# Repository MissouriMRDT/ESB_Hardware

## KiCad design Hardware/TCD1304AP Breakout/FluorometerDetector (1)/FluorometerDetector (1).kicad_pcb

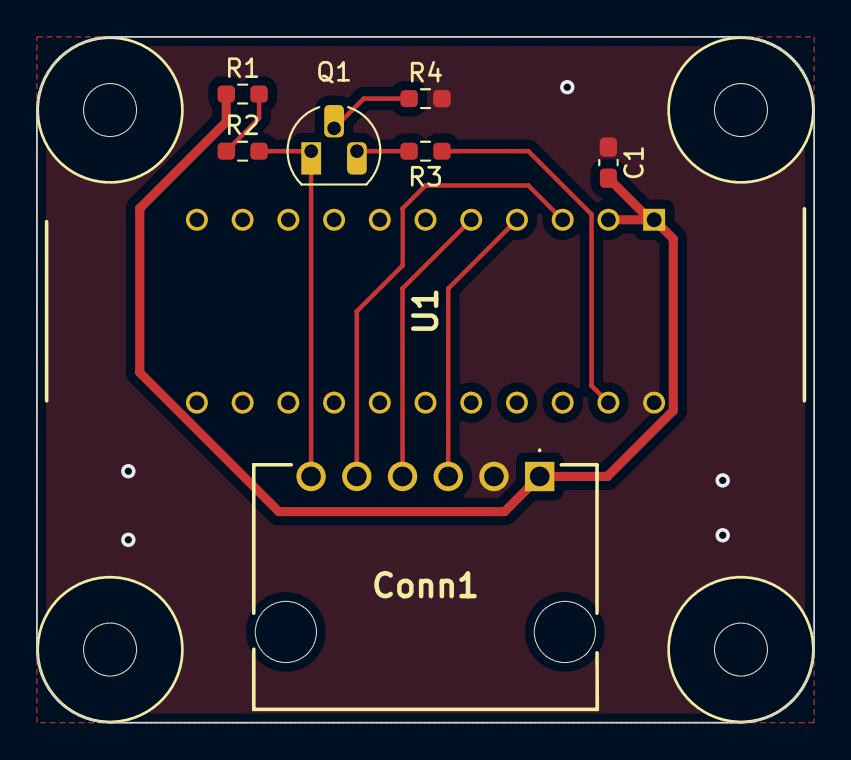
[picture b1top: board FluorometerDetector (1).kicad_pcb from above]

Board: 2 copper layers, 43.2 x 38.1 mm, 12 parts (0 on the bottom side), 10 nets.

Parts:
C1: 10uF; C_0603_1608Metric_Pad1.08x0.95mm_HandSolder
Conn1: Molex_SL_06; 705550040
Q1: Q_PNP_BCE; TO-92_HandSolder
R1: 1.2k; R_0603_1608Metric_Pad0.98x0.95mm_HandSolder
R2: 1k; R_0603_1608Metric_Pad0.98x0.95mm_HandSolder
R3, R4: 150; R_0603_1608Metric_Pad0.98x0.95mm_HandSolder
U1: TCD1304; DIP1016W62P254L4160H372Q22N
V1, V2, V3, V4: Via; 4_40_Hole

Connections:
+3V3: C1.2, Conn1.1, R1.1, U1.1 (VDD), U1.2 (VAD)
GND: C1.1, Conn1.2, R4.2, U1.22 (SS)
unnamed: Conn1.3, U1.4 (M)
unnamed: Conn1.4, U1.5 (SH)
unnamed: Conn1.5, U1.3 (ICG)
unnamed: Conn1.6, Q1.1 (E), R2.2
unnamed: Q1.2 (C), R4.1
unnamed: Q1.3 (B), R3.2
unnamed: R1.2, R2.1
unnamed: R3.1, U1.21 (OS)

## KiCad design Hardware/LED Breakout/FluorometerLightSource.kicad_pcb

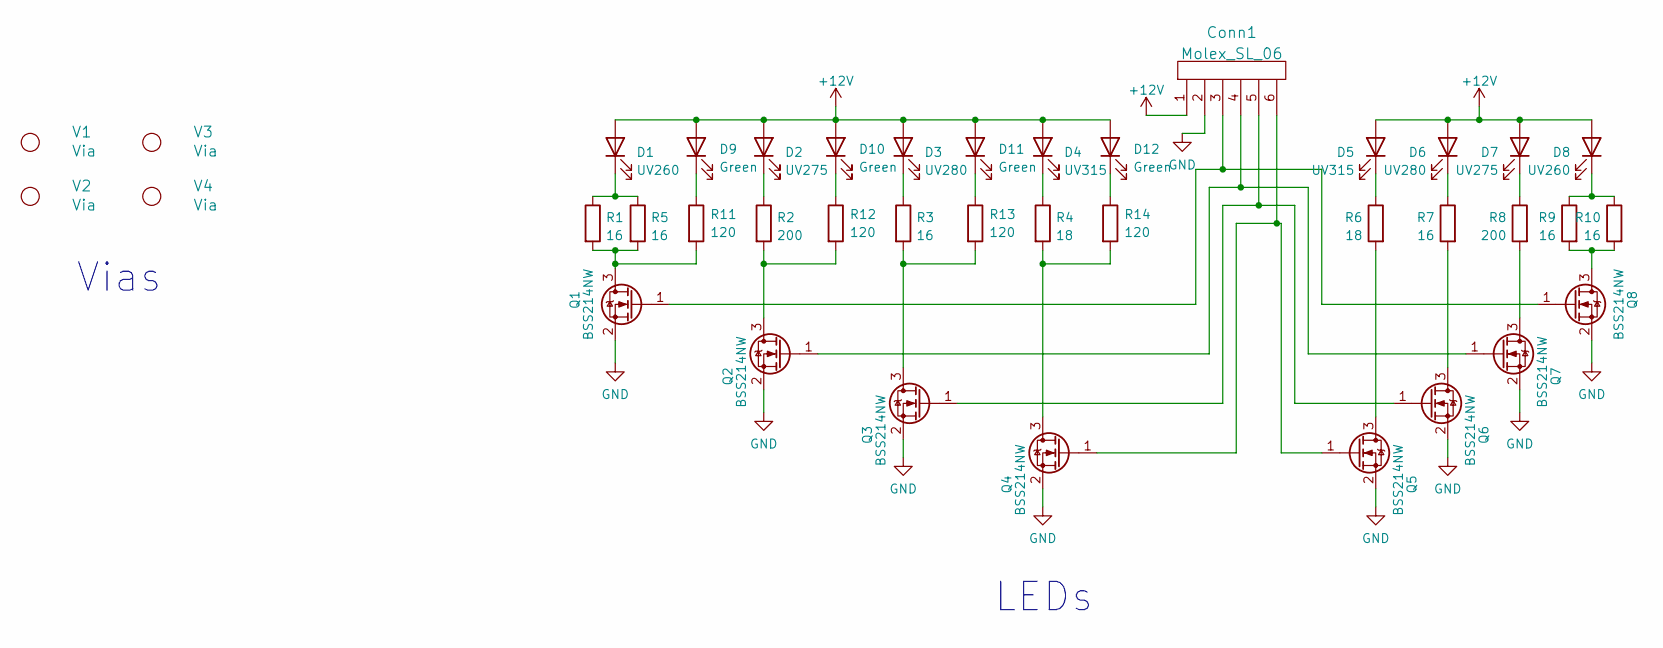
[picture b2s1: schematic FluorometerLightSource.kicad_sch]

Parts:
Conn1: Molex_SL_06; 705550040
D1, D8: UV260; KL26550USMWD
D2, D7: UV275; SUCULBN1VCAGAY674F4G30R18
D3, D6: UV280; XBT3535UVA130CD27501
D4, D5: UV315; WS3535C48LF-310
D9, D10, D11, D12: Green; LED_0603_1608Metric_Pad1.05x0.95mm_HandSolder
Q1, Q2, Q3, Q4, Q5, Q6, Q7, Q8: BSS214NW; SOT-323_SC-70
R1, R3, R5, R7, R9, R10: 16; R_2512_6332Metric_Pad1.40x3.35mm_HandSolder
R2, R8: 200; R_0603_1608Metric_Pad0.98x0.95mm_HandSolder
R4, R6: 18; R_2512_6332Metric_Pad1.40x3.35mm_HandSolder
R11, R12, R13, R14: 120; R_0603_1608Metric_Pad0.98x0.95mm_HandSolder
V1, V2, V3, V4: Via; 4_40_Hole

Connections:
+12V: Conn1.1, D1.2 (A), D2.2 (A), D3.2 (A), D4.2 (A), D5.2 (A), D6.2 (A), D7.2 (A), D8.2 (A), D9.2 (A), D10.2 (A), D11.2 (A), D12.2 (A)
GND: Conn1.2, Q1.2 (S), Q2.2 (S), Q3.2 (S), Q4.2 (S), Q5.2 (S), Q6.2 (S), Q7.2 (S), Q8.2 (S)
unnamed: Conn1.3, Q1.1 (G), Q8.1 (G)
unnamed: Conn1.4, Q2.1 (G), Q7.1 (G)
unnamed: Conn1.5, Q3.1 (G), Q6.1 (G)
unnamed: Conn1.6, Q4.1 (G), Q5.1 (G)
unnamed: D1.1 (K), R1.1, R5.1
unnamed: D2.1 (K), R2.1
unnamed: D3.1 (K), R3.1
unnamed: D4.1 (K), R4.1
unnamed: D5.1 (K), R6.1
unnamed: D6.1 (K), R7.1
unnamed: D7.1 (K), R8.1
unnamed: D8.1 (K), R9.1, R10.1
unnamed: D9.1 (K), R11.1
unnamed: D10.1 (K), R12.1
unnamed: D11.1 (K), R13.1
unnamed: D12.1 (K), R14.1
unnamed: Q1.3 (D), R1.2, R5.2, R11.2
unnamed: Q2.3 (D), R2.2, R12.2
unnamed: Q3.3 (D), R3.2, R13.2
unnamed: Q4.3 (D), R4.2, R14.2
unnamed: Q5.3 (D), R6.2
unnamed: Q6.3 (D), R7.2
unnamed: Q7.3 (D), R8.2
unnamed: Q8.3 (D), R9.2, R10.2

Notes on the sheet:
LEDs
Vias

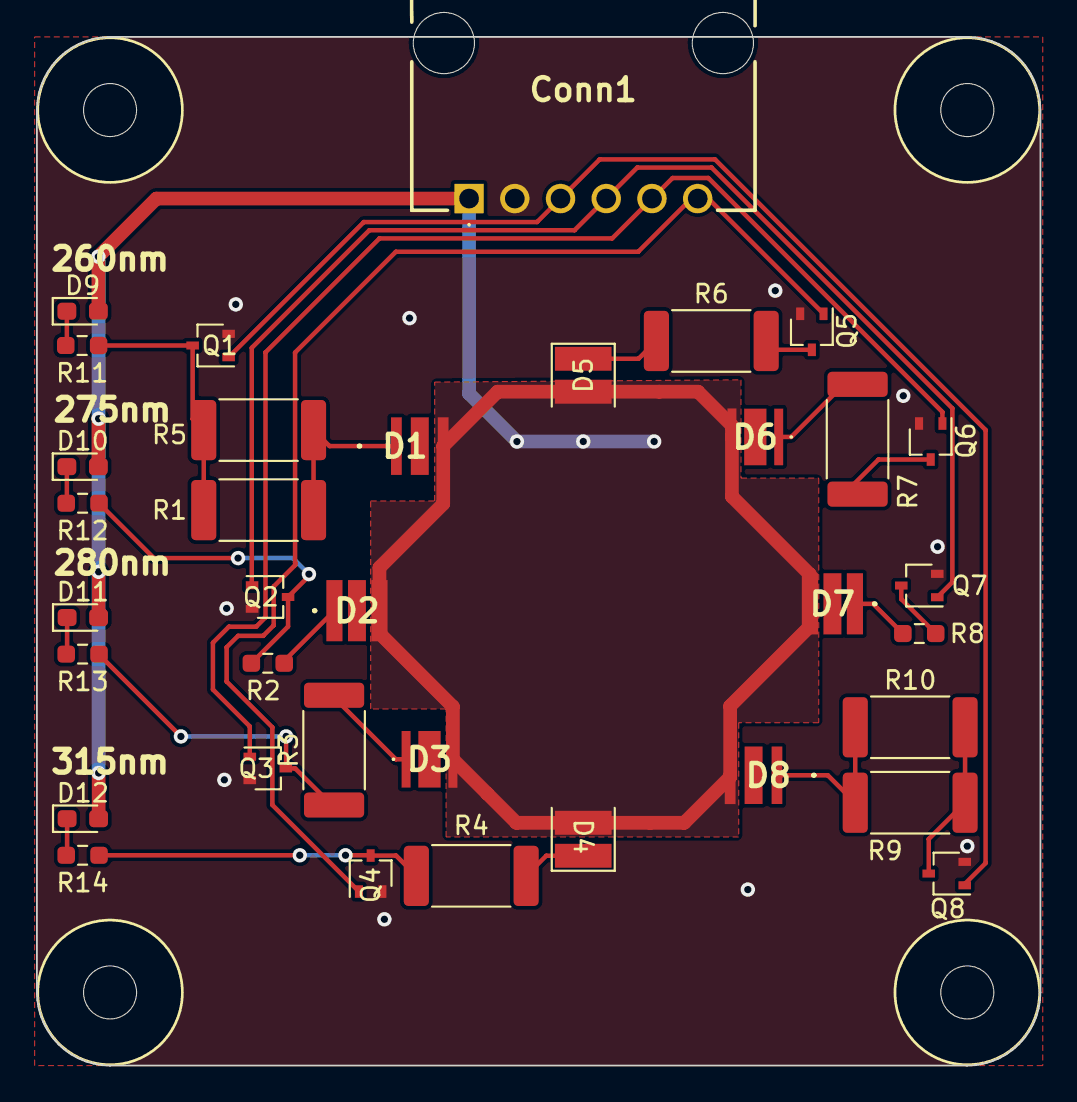
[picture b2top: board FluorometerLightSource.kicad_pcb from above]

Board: 2 copper layers, 55.8 x 57.1 mm, 39 parts (0 on the bottom side), 26 nets.

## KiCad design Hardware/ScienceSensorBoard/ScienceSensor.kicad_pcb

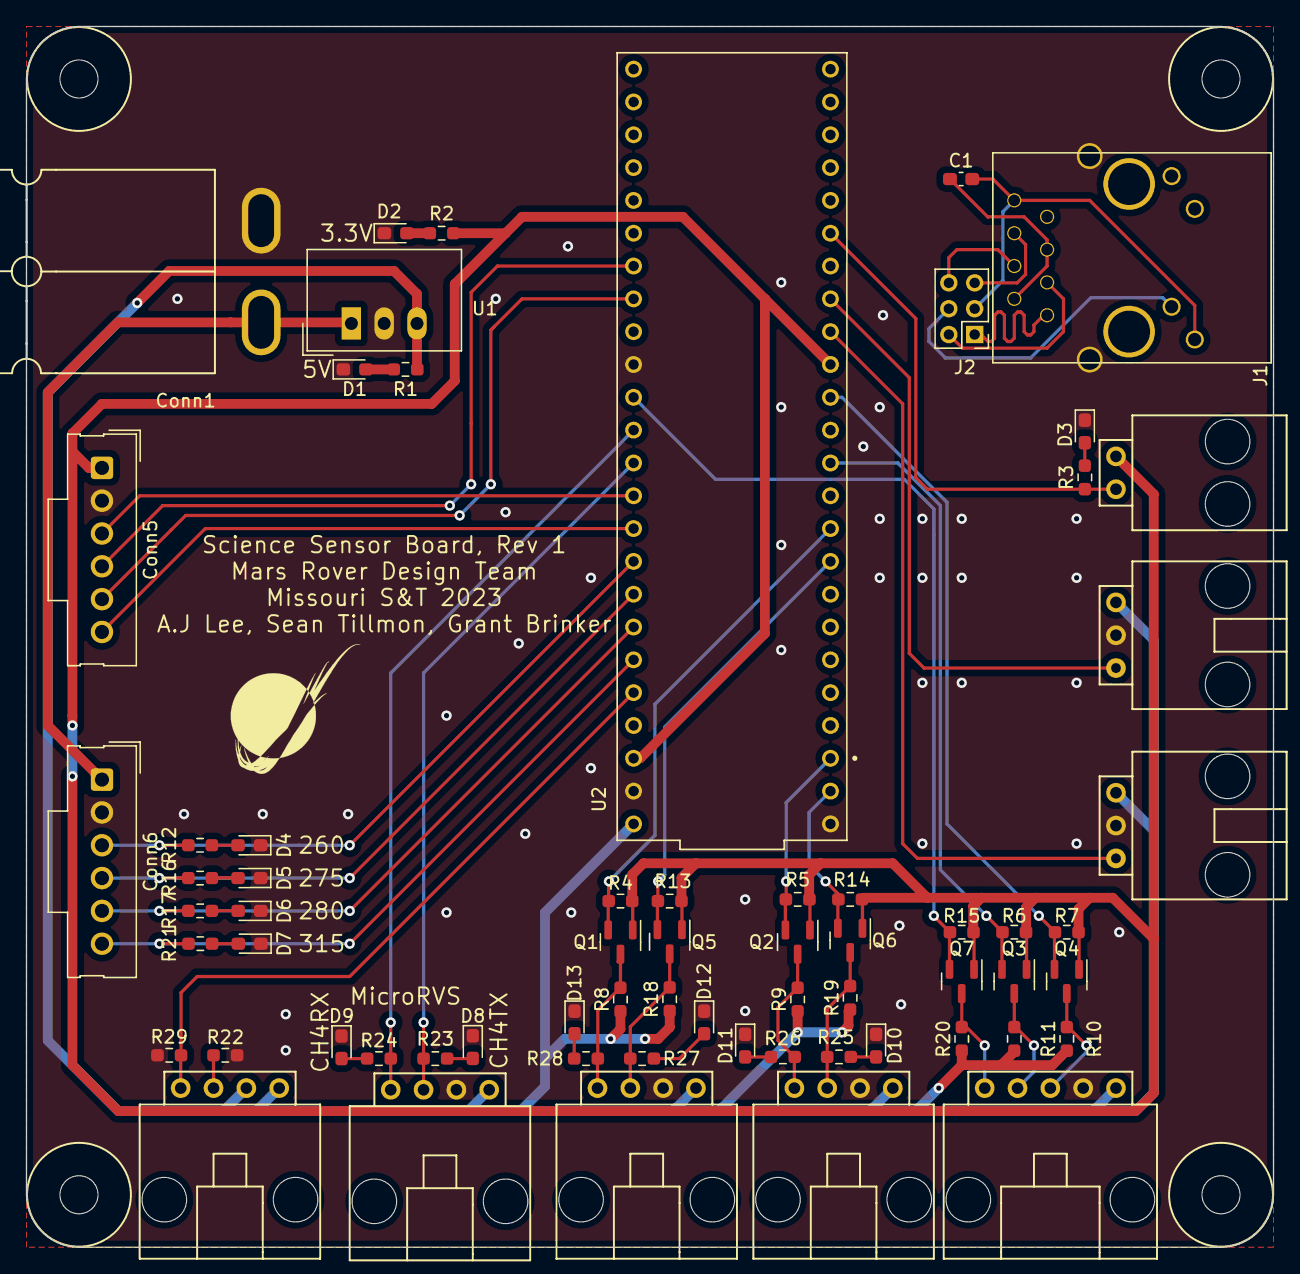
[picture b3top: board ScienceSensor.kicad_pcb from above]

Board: 2 copper layers, 96.5 x 94.5 mm, 69 parts (0 on the bottom side), 53 nets.

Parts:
C1: 0.1uF; C_0603_1608Metric_Pad1.08x0.95mm_HandSolder
Conn1: AndersonPP; Square_Anderson_2_H_Side_By_Side
Conn2: Molex_SL_02; MOLEX_SL_02_Horizontal
Conn3, Conn4: Molex_SL_03; MOLEX_SL_03_Horizontal
Conn5, Conn6: Molex_SL_06; Molex_SL_171971-0006_1x06_P2.54mm_Vertical
Conn7, Conn8, Conn9, Conn10: Molex_SL_04; MOLEX_SL_04_Horizontal
Conn11: Molex_SL_05; MOLEX_SL_05_Horizontal
D1, D2: Green; LED_0603_1608Metric_Pad1.05x0.95mm_HandSolder
D3: Yellow; LED_0603_1608Metric_Pad1.05x0.95mm_HandSolder
D4, D5, D6, D7, D8, D9, D10, D11, D12, D13: Blue; LED_0603_1608Metric_Pad1.05x0.95mm_HandSolder
J1: RJ45_LED_Shielded; RJ45_Teensy
J2: Conn_02x03_Counter_Clockwise; PinHeader_2x03_P2.00mm_Vertical
Q1, Q2, Q3, Q4, Q5, Q6, Q7: BSS138; SOT-23
R1, R23, R24, R25, R26, R27, R28: 330; R_0603_1608Metric_Pad0.98x0.95mm_HandSolder
R2, R3, R12, R16, R17, R21: 120; R_0603_1608Metric_Pad0.98x0.95mm_HandSolder
R4, R5, R6, R7, R8, R9, R10, R11, R13, R14, R15, R18, R19, R20, R29: 10K; R_0603_1608Metric_Pad0.98x0.95mm_HandSolder
R22: 93.1; R_0603_1608Metric_Pad0.98x0.95mm_HandSolder
U1: TSR_1-2450; Converter_DCDC_TRACO_TSR-1_THT
U2: Teensy4.1_DEV-16771; Teensy_4_1_Bare
V1, V2, V3, V4: Via; 4_40_Hole

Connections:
+3V3: Conn2.1, Conn5.1, Q1.1 (G), Q2.1 (G), Q3.1 (G), Q4.1 (G), Q5.1 (G), Q6.1 (G), Q7.1 (G), R2.2, R4.1, R5.1, R6.1, R7.1, R13.1, R14.1, R15.1, U2.3.3V_1 (3.3V), U2.3.3V_2 (3.3V)
+5V: Conn3.1, Conn4.1, Conn7.1, Conn8.1, Conn8.2, Conn9.1, Conn10.1, Conn11.1, R1.2, R8.1, R9.1, R10.1, R11.1, R18.1, R19.1, R20.1, U1.3 (Vout), U2.VIN
+12V: Conn1.2 (V+Log), Conn6.1, U1.1 (Vin)
/Rx+: J1.4, J2.6
/Rx-: J1.6, J2.5
/Tx+: J1.1, J2.1
/Tx-: J1.3, J2.2
CCD_ICG: Conn5.5, U2.40 (A16)
CCD_MC: Conn5.3, U2.16 (A2)
CCD_OS: Conn5.6, U2.17 (A3)
CCD_SH: Conn5.4, U2.39 (A15)
CH4_RX: Conn7.4, R24.2, U2.14 (A0)
CH4_TX: Conn7.3, R23.2, U2.15 (A1)
CO2_RX: Conn9.4, Q2.3 (D), R9.2, R26.2
CO2_TX: Conn9.3, Q6.3 (D), R19.2, R25.2
GND: Conn1.1 (GND), Conn3.2, Conn4.2, Conn5.2, Conn6.2, Conn7.2, Conn9.2, Conn10.2, Conn11.2, D1.1 (K), D2.1 (K), D3.1 (K), D4.1 (K), D5.1 (K), D6.1 (K), D7.1 (K), D8.1 (K), D9.1 (K), D10.1 (K), D11.1 (K), D12.1 (K), D13.1 (K), J1.SH, R22.1, R29.1, U1.2 (GND), U2.GND1 (GND), U2.GND2 (GND), U2.GND3 (GND)
LED_260: Conn6.3, R12.2, U2.18 (A4)
LED_275: Conn6.4, R16.2, U2.19 (A5)
LED_280: Conn6.5, R17.2, U2.20 (A6)
LED_315: Conn6.6, R21.2, U2.21 (A7)
Micro_LIM: Conn2.2, R3.1, U2.27 (A13)
Micro_Servo1: Conn4.3, U2.25 (A11)
Micro_Servo2: Conn3.3, U2.24 (A10)
NH3: Conn8.4, R29.2, U2.22 (A8)
NO2_CS: Conn11.4, Q3.3 (D), R10.2
NO2_MISO: Conn11.3, Q4.3 (D), R11.2
NO2_SCK: Conn11.5, Q7.3 (D), R20.2
unnamed: C1.1, J1.2, J1.5
unnamed: C1.2, J1.8, J1.9, J2.3
unnamed: Conn8.3, R22.2
unnamed: D1.2 (A), R1.1
unnamed: D2.2 (A), R2.1
unnamed: D3.2 (A), R3.2
unnamed: D4.2 (A), R12.1
unnamed: D5.2 (A), R16.1
unnamed: D6.2 (A), R17.1
unnamed: D7.2 (A), R21.1
unnamed: D8.2 (A), R23.1
unnamed: D9.2 (A), R24.1
unnamed: D10.2 (A), R25.1
unnamed: D11.2 (A), R26.1
unnamed: D12.2 (A), R27.1
unnamed: D13.2 (A), R28.1
unnamed: J1.10, J2.4
O2_RX: Conn10.4, Q1.3 (D), R8.2, R28.2
O2_TX: Conn10.3, Q5.3 (D), R18.2, R27.2
Teensy_CO2_RX: Q6.2 (S), R14.2, U2.0 (RX1)
Teensy_CO2_TX: Q2.2 (S), R5.2, U2.1 (TX1)
Teensy_NO2_CS: Q3.2 (S), R6.2, U2.10 (CS1)
Teensy_NO2_MISO: Q4.2 (S), R7.2, U2.12 (MISO)
Teensy_NO2_SCK: Q7.2 (S), R15.2, U2.13 (SCK)
Teensy_O2_RX: Q5.2 (S), R13.2, U2.7 (RX2)
Teensy_O2_TX: Q1.2 (S), R4.2, U2.8 (TX2)

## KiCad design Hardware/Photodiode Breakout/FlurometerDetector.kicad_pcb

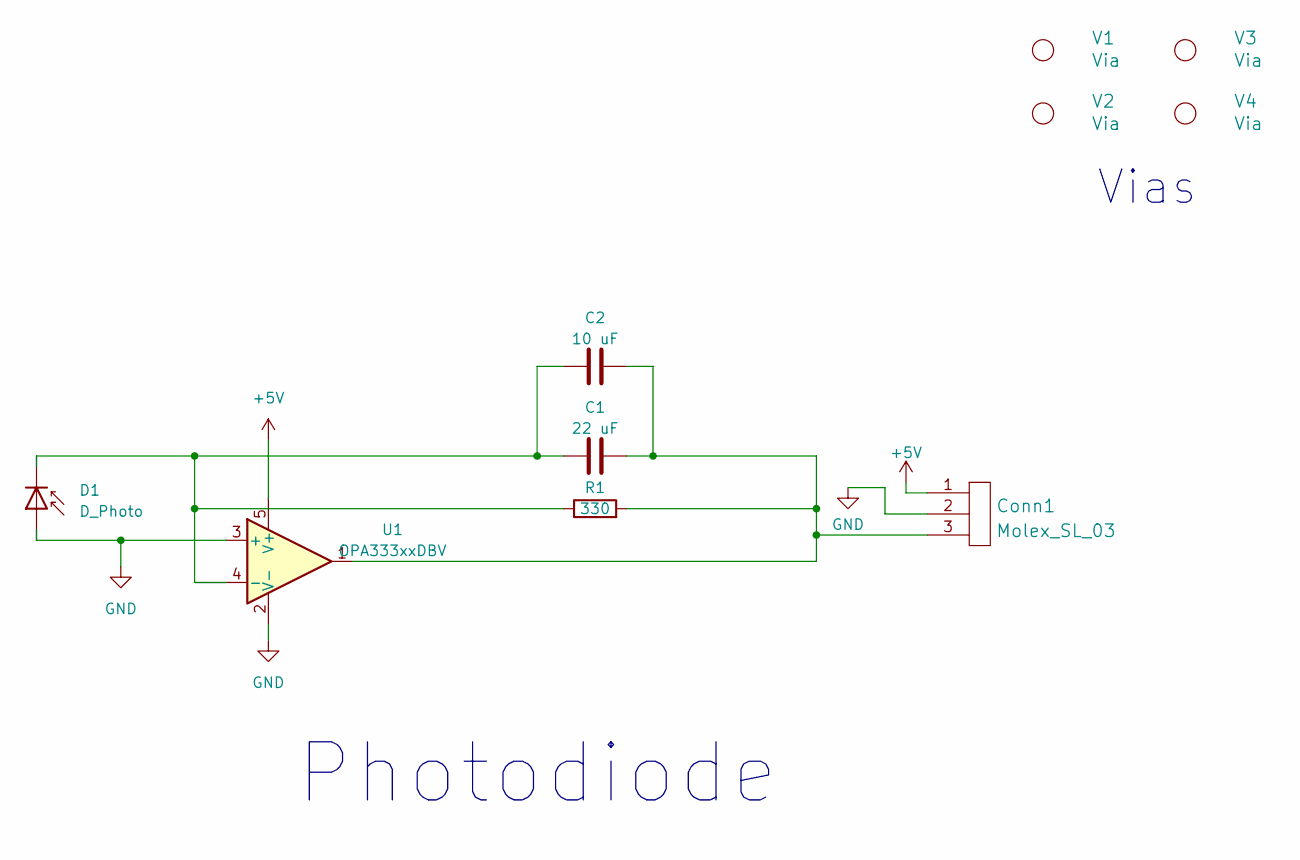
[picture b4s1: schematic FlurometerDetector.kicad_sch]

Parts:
C1: 22 uF; C_0603_1608Metric_Pad1.08x0.95mm_HandSolder
C2: 10 uF; C_0603_1608Metric_Pad1.08x0.95mm_HandSolder
Conn1: Molex_SL_03; MOLEX_SL_03_Horizontal
D1: D_Photo; TO-18-2
R1: 330; R_0603_1608Metric_Pad0.98x0.95mm_HandSolder
U1: OPA333xxDBV; SOT-23-5
V1, V2, V3, V4: Via; 4_40_Hole

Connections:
+5V: Conn1.1, U1.5 (V+)
GND: Conn1.2, D1.2 (A), U1.2 (V-), U1.3 (+)
unnamed: C1.1, C2.1, D1.1 (K), R1.1, U1.4 (-)
unnamed: C1.2, C2.2, Conn1.3, R1.2, U1.1

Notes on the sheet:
Vias
Photodiode

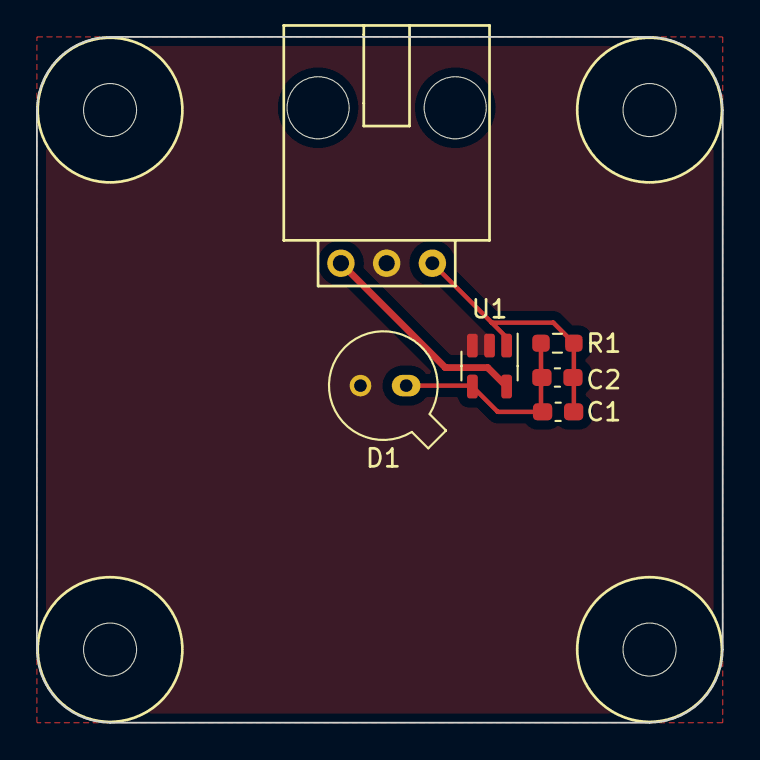
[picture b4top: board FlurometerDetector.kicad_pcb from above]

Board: 2 copper layers, 38.1 x 38.1 mm, 10 parts (0 on the bottom side), 4 nets.

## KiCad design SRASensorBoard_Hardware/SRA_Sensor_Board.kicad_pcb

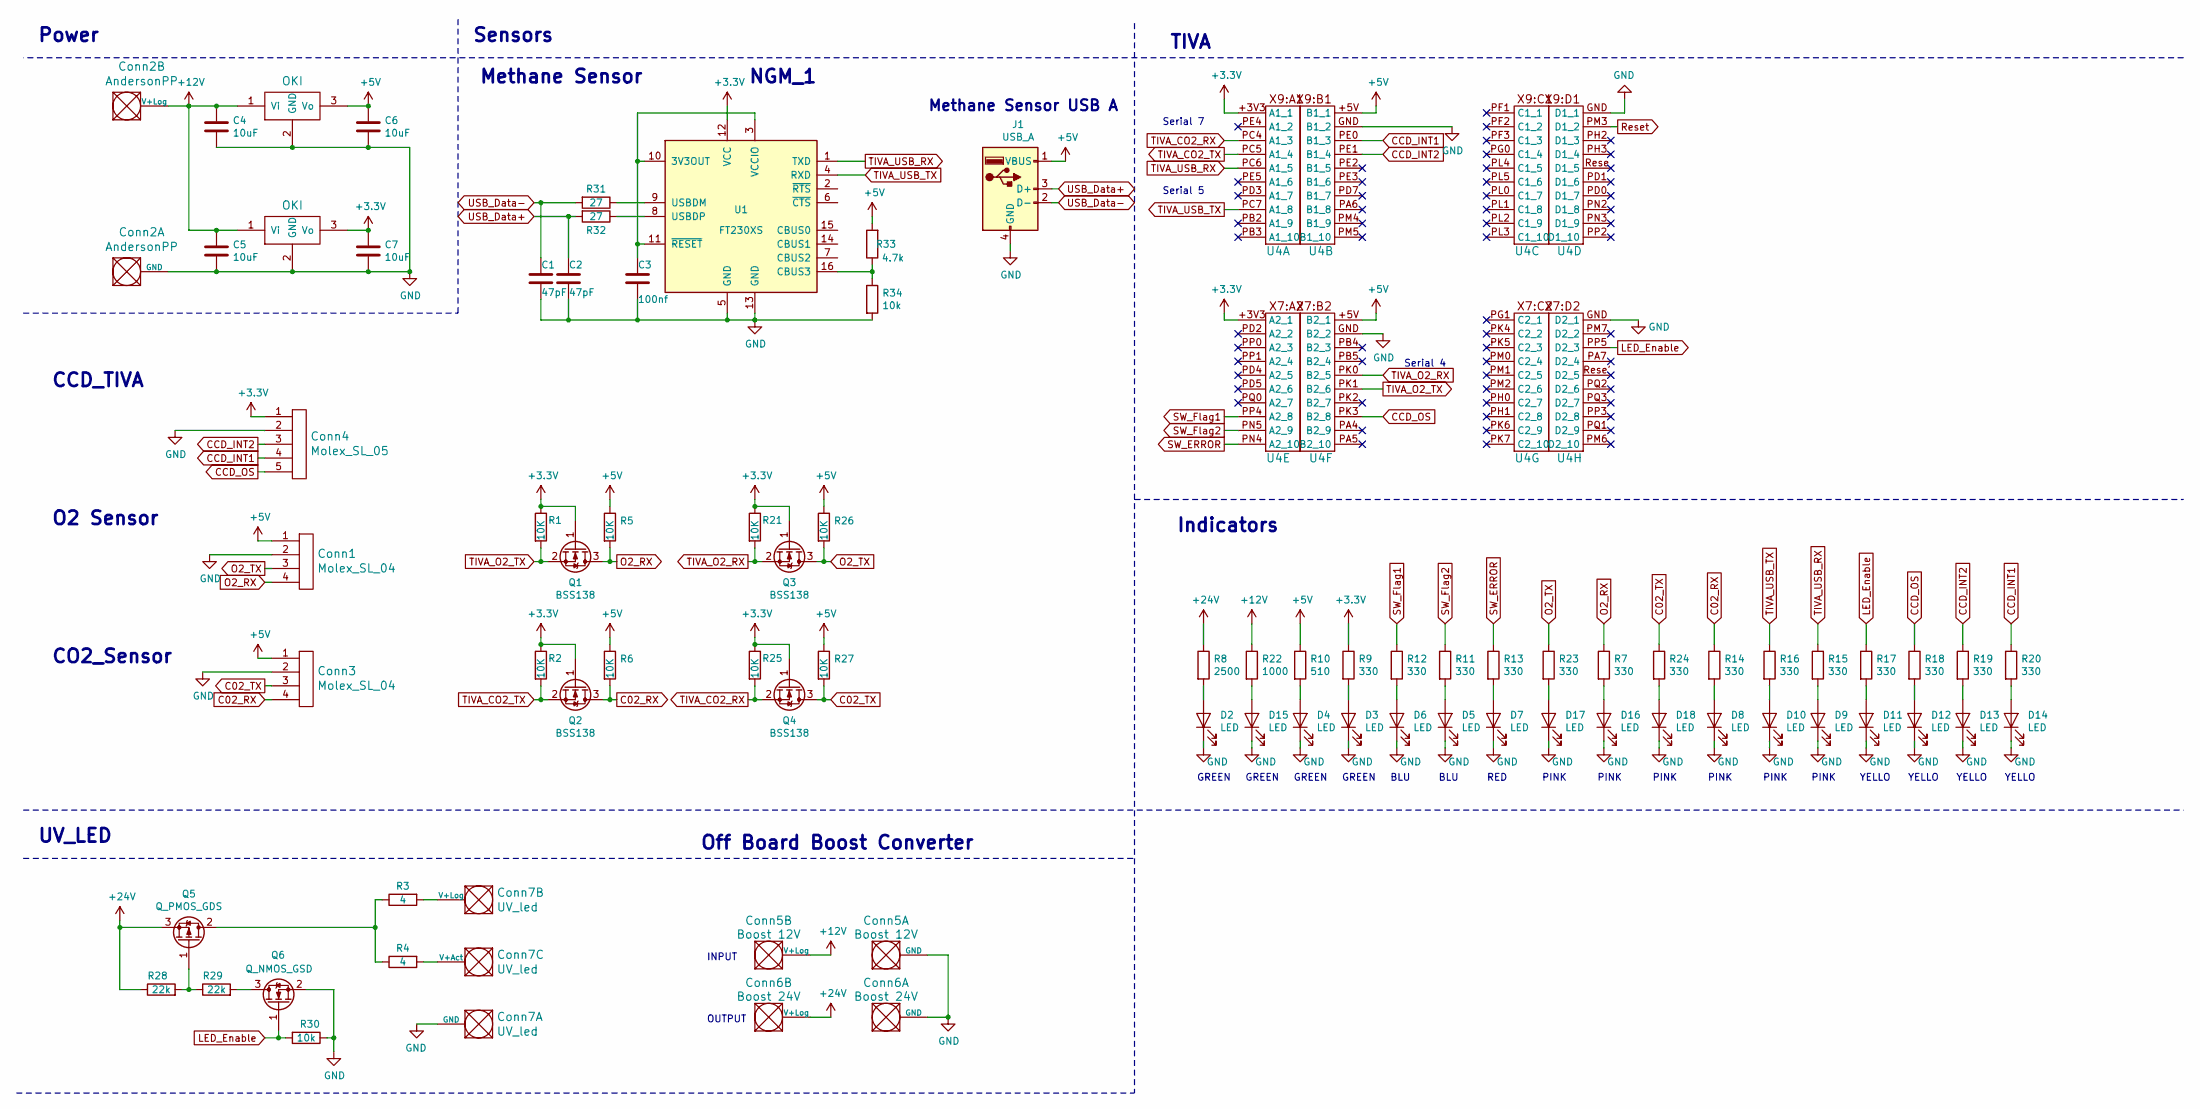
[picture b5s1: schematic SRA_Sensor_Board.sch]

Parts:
C1, C2: 47pF; C_0603_1608Metric_Pad1.05x0.95mm_HandSolder
C3: 100nf; C_0603_1608Metric_Pad1.05x0.95mm_HandSolder
C4, C5, C6, C7: 10uF; C_0603_1608Metric_Pad1.05x0.95mm_HandSolder
Conn1, Conn3: Molex_SL_04; MOLEX_SL_04_Vertical
Conn2: AndersonPP; Anderson_2_Horizontal_Side_by_Side
Conn4: Molex_SL_05; MOLEX_SL_05_Vertical
Conn5: Boost 12V; Anderson_2_Horizontal_Side_by_Side
Conn6: Boost 24V; Anderson_2_Horizontal_Side_by_Side
Conn7: UV_led; Anderson_3_Horizontal_Side_by_Side
D2, D3, D4, D5, D6, D7, D8, D9, D10, D11, D12, D13, D14, D15, D16, D17, D18: LED; D_0603_1608Metric_Pad1.05x0.95mm_HandSolder
J1: USB_A; 292303-1
Q1, Q2, Q3, Q4: BSS138; SOT-23
Q5: Q_PMOS_GDS; TO-252-2
Q6: Q_NMOS_GSD; SOT-23
R1, R2, R5, R6, R21, R25, R26, R27: 10K; R_0603_1608Metric_Pad1.05x0.95mm_HandSolder
R3, R4: 4; R_Axial_DIN0414_L11.9mm_D4.5mm_P15.24mm_Horizontal
R7, R9, R11, R12, R13, R14, R15, R16, R17, R18, R19, R20, R23, R24: 330; R_0603_1608Metric_Pad1.05x0.95mm_HandSolder
R8: 2500; R_0603_1608Metric_Pad1.05x0.95mm_HandSolder
R10: 510; R_0603_1608Metric_Pad1.05x0.95mm_HandSolder
R22: 1000; R_0603_1608Metric_Pad1.05x0.95mm_HandSolder
R28, R29: 22k; R_0603_1608Metric_Pad1.05x0.95mm_HandSolder
R30, R34: 10k; R_0603_1608Metric_Pad1.05x0.95mm_HandSolder
R31, R32: 27; R_0603_1608Metric_Pad1.05x0.95mm_HandSolder
R33: 4.7k; R_0603_1608Metric_Pad1.05x0.95mm_HandSolder
U1: FT230XS; SSOP-16_3.9x4.9mm_P0.635mm
U2, U3: OKI; OKI_Horizontal
U4: TM4C129E_Launchpad; TM4C129E_Launchpad_FULL_THT_BOTTOM

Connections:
+3V3: C7.1, Conn4.1, Q1.1 (G), Q2.1 (G), Q3.1 (G), Q4.1 (G), R1.1, R2.1, R9.1, R21.1, R25.1, U1.12 (VCC), U3.3 (Vo), U4.+3V3 (A1_1)
+5V: C6.1, Conn1.1, Conn3.1, J1.1 (VBUS), R5.1, R6.1, R10.1, R26.1, R27.1, R33.2, U2.3 (Vo), U4.+5V (B1_1)
+12V: C4.1, C5.1, Conn2.2 (V+Log), Conn5.2 (V+Log), R22.1, U2.1 (Vi), U3.1 (Vi)
+24V: Conn6.2 (V+Log), Q5.3 (S), R8.1, R28.1
C02_RX: Conn3.4, Q2.3 (D), R6.2, R14.1
C02_TX: Conn3.3, Q4.3 (D), R24.1, R27.2
CCD_INT1: Conn4.4, R20.1, U4.PE0 (B1_3)
CCD_INT2: Conn4.3, R19.1, U4.PE1 (B1_4)
CCD_OS: Conn4.5, R18.1, U4.PK3 (B2_8)
GND: C1.2, C2.2, C3.2, C4.2, C5.2, C6.2, C7.2, Conn1.2, Conn2.1 (GND), Conn3.2, Conn4.2, Conn5.1 (GND), Conn6.1 (GND), Conn7.1 (GND), D2.1 (K), D3.1 (K), D4.1 (K), D5.1 (K), D6.1 (K), D7.1 (K), D8.1 (K), D9.1 (K), D10.1 (K), D11.1 (K), D12.1 (K), D13.1 (K), D14.1 (K), D15.1 (K), D16.1 (K), D17.1 (K), D18.1 (K), J1.4 (GND), Q6.2 (S), R30.1, R34.2, U1.5 (GND), U1.13 (GND), U2.2 (GND), U3.2 (GND), U4.GND (B1_2)
LED_Enable: Q6.1 (G), R17.1, R30.2, U4.PP5 (D2_3)
unnamed: C3.1, U1.3 (VCCIO), U1.10 (3V3OUT), U1.11 (~RESET)
unnamed: Conn7.2 (V+Log), R3.2
unnamed: Conn7.3 (V+Act), R4.2
unnamed: D2.2 (A), R8.2
unnamed: D3.2 (A), R9.2
unnamed: D4.2 (A), R10.2
unnamed: D5.2 (A), R11.2
unnamed: D6.2 (A), R12.2
unnamed: D7.2 (A), R13.2
unnamed: D8.2 (A), R14.2
unnamed: D9.2 (A), R15.2
unnamed: D10.2 (A), R16.2
unnamed: D11.2 (A), R17.2
unnamed: D12.2 (A), R18.2
unnamed: D13.2 (A), R19.2
unnamed: D14.2 (A), R20.2
unnamed: D15.2 (A), R22.2
unnamed: D16.2 (A), R7.2
unnamed: D17.2 (A), R23.2
unnamed: D18.2 (A), R24.2
unnamed: Q5.1 (G), R28.2, R29.1
unnamed: Q5.2 (D), R3.1, R4.1
unnamed: Q6.3 (D), R29.2
unnamed: R31.1, U1.9 (USBDM)
unnamed: R32.1, U1.8 (USBDP)
unnamed: R33.1, R34.1, U1.16 (CBUS3)
O2_RX: Conn1.4, Q1.3 (D), R5.2, R7.1
O2_TX: Conn1.3, Q3.3 (D), R23.1, R26.2
Reset: U4.PM3 (D1_2)
SW_ERROR: R13.1, U4.PN4 (A2_10)
SW_Flag1: R12.1, U4.PP4 (A2_8)
SW_Flag2: R11.1, U4.PN5 (A2_9)
TIVA_CO2_RX: Q4.2 (S), R25.2, U4.PC4 (A1_3)
TIVA_CO2_TX: Q2.2 (S), R2.2, U4.PC5 (A1_4)
TIVA_O2_RX: Q3.2 (S), R21.2, U4.PK0 (B2_5)
TIVA_O2_TX: Q1.2 (S), R1.2, U4.PK1 (B2_6)
TIVA_USB_RX: R15.1, U1.1 (TXD), U4.PC6 (A1_5)
TIVA_USB_TX: R16.1, U1.4 (RXD), U4.PC7 (A1_8)
USB_Data+: C2.1, J1.3 (D+), R32.2
USB_Data-: C1.1, J1.2 (D-), R31.2

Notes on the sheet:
Power
YELLO
YELLO
PINK
PINK
RED
BLU
GREEN
Sensors
TIVA
UV_LED
CCD_TIVA
NGM_1
O2 Sensor
Off Board Boost Converter
CO2_Sensor
Methane Sensor
Indicators
Methane Sensor USB A
INPUT
OUTPUT
Serial 5
Serial 7
Serial 4

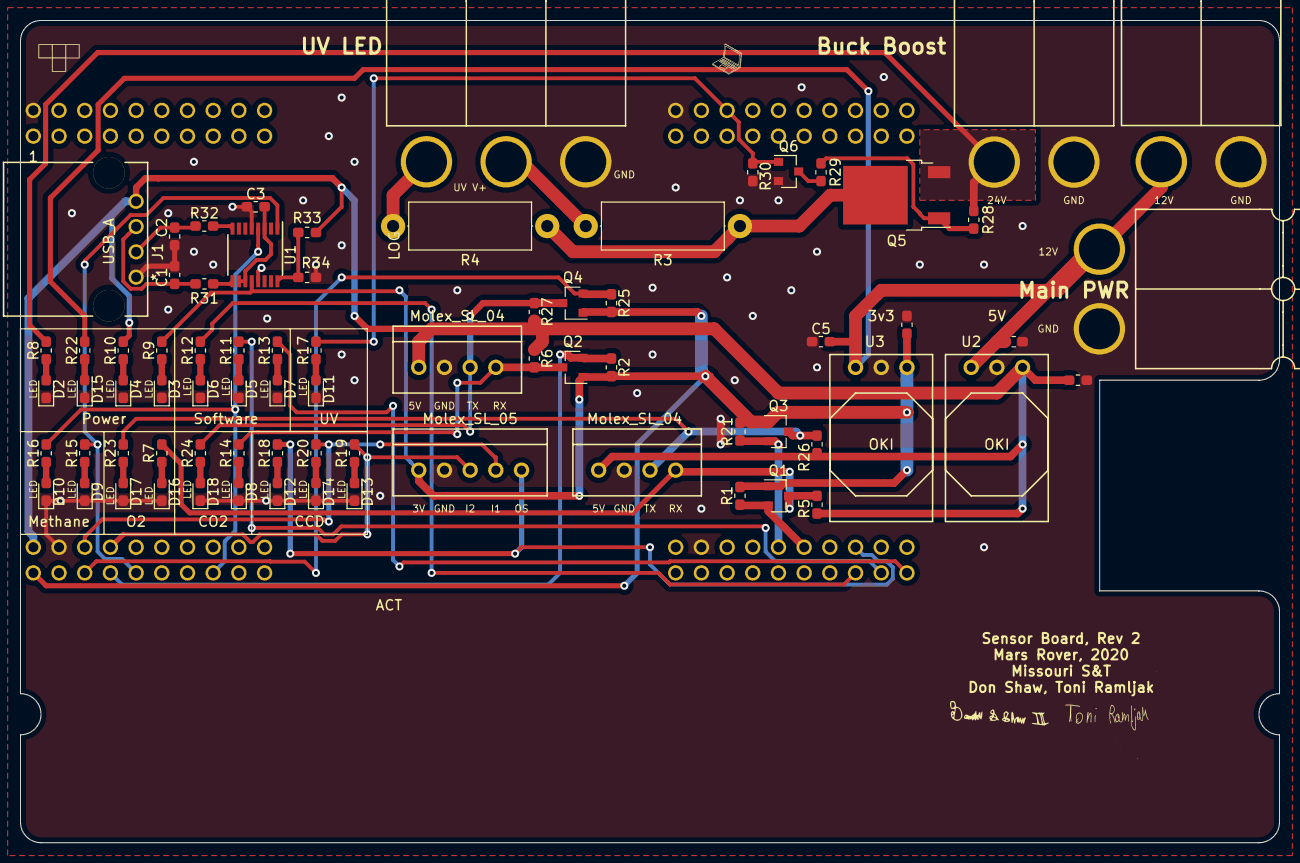
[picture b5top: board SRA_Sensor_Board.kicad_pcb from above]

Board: 2 copper layers, 124.5 x 81.3 mm, 76 parts (0 on the bottom side), 50 nets.

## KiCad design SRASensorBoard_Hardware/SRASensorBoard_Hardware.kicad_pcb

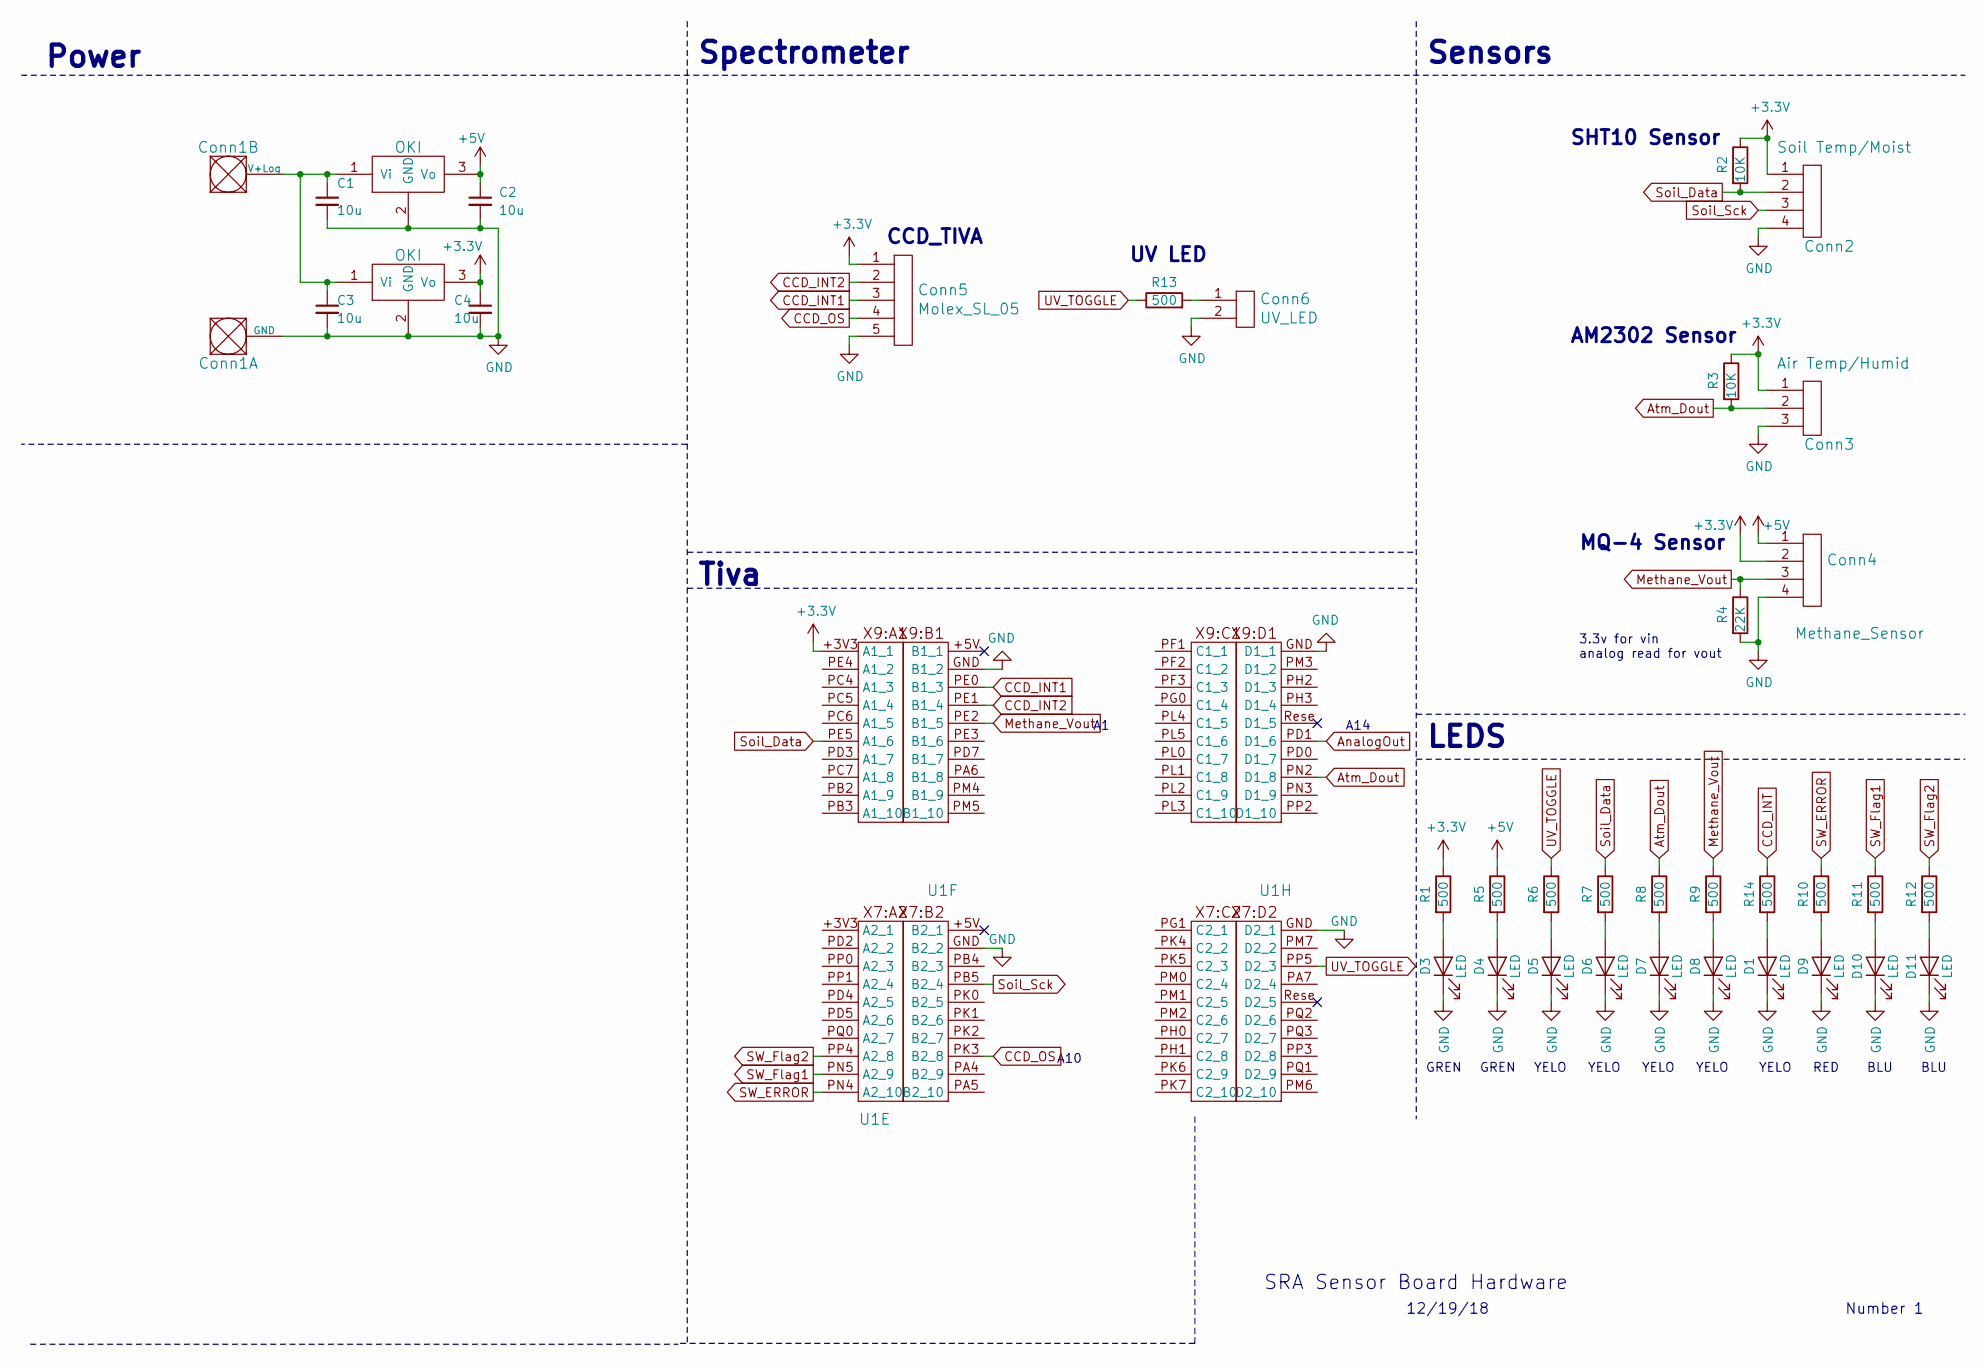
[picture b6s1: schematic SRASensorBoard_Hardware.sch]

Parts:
C1, C2, C3, C4: 10u; C_0603_1608Metric_Pad1.05x0.95mm_HandSolder
Conn1: AndersonPP; Anderson_2_Horisontal_Side_by_Side
Conn2: Soil Temp/Moist; MOLEX_SL_04_Horizontal
Conn3: Air Temp/Humid; MOLEX_SL_03_Horizontal
Conn4: Methane_Sensor; MOLEX_SL_04_Horizontal
Conn5: Molex_SL_05; MOLEX_SL_05_Horizontal
Conn6: UV_LED; MOLEX_SL_02_Horizontal
D1, D3, D4, D5, D6, D7, D8, D9, D10, D11: LED; D_0603_1608Metric_Pad1.05x0.95mm_HandSolder
R1, R5, R6, R7, R8, R9, R10, R11, R12, R13, R14: 500; R_0603_1608Metric_Pad1.05x0.95mm_HandSolder
R2, R3: 10K; R_0603_1608Metric_Pad1.05x0.95mm_HandSolder
R4: 22K; R_0603_1608Metric_Pad1.05x0.95mm_HandSolder
U1: Tive Header; TM4C129E_Launchpad_FULL
U2, U3: OKI; OKI_Horizontal

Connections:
+3V3: C4.1, Conn2.1, Conn3.1, Conn4.2, Conn5.1, R1.1, R2.1, R3.1, U1.+3V3 (A1_1), U3.3 (Vo)
+5V: C2.1, Conn4.1, R5.1, U2.3 (Vo)
Atm_Dout: Conn3.2, R3.2, R8.1, U1.PN2 (D1_8)
CCD_INT2: Conn5.2, U1.PE1 (B1_4); also elsewhere on the board
CCD_OS: Conn5.4, U1.PK3 (B2_8)
GND: C1.2, C2.2, C3.2, C4.2, Conn1.1 (GND), Conn2.4, Conn3.3, Conn4.4, Conn5.5, Conn6.2, D1.1 (K), D3.1 (K), D4.1 (K), D5.1 (K), D6.1 (K), D7.1 (K), D8.1 (K), D9.1 (K), D10.1 (K), D11.1 (K), R4.2, U1.GND (B1_2), U2.2 (GND), U3.2 (GND); also elsewhere on the board
Methane_Vout: Conn4.3, R4.1, R9.1, U1.PE2 (B1_5)
unnamed: C1.1, C3.1, Conn1.2 (V+Log), U2.1 (Vi), U3.1 (Vi)
unnamed: Conn6.1, R13.2
unnamed: D1.2 (A), R14.2
unnamed: D3.2 (A), R1.2
unnamed: D4.2 (A), R5.2
unnamed: D5.2 (A), R6.2
unnamed: D6.2 (A), R7.2
unnamed: D7.2 (A), R8.2
unnamed: D8.2 (A), R9.2
unnamed: D9.2 (A), R10.2
unnamed: D10.2 (A), R11.2
unnamed: D11.2 (A), R12.2
SW_ERROR: R10.1, U1.PN4 (A2_10)
SW_Flag1: R11.1, U1.PN5 (A2_9)
SW_Flag2: R12.1, U1.PP4 (A2_8)
Soil_Data: Conn2.2, R2.2, R7.1, U1.PE5 (A1_6)
Soil_Sck: Conn2.3, U1.PB5 (B2_4)
UV_TOGGLE: R6.1, R13.1, U1.PP5 (D2_3)

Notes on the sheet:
Sensors
Power
3.3v for vin analog read for vout
Spectrometer
CCD_TIVA
UV LED
SHT10 Sensor
AM2302 Sensor
MQ-4 Sensor
LEDS
Tiva
RED
BLU
GREN
YELO
12/19/18
SRA Sensor Board Hardware
Number 1
A14
YELO
A10

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

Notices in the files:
parts and their libraries:
Copyright 2016 Accelerated Designs. All rights reserved.
